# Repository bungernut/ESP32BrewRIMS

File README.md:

# ESP32BrewREMS

# Documentation
I dont know why, but it's been a real pain to find documentation for the ESP32 device. I'm using a HiLetgo ESP32 OLED WiFi Kit V3. This is apparently really a product by Heltec: https://heltec.org/project/wifi-kit32-v3/

USB-Serial Driver: https://www.silabs.com/developer-tools/usb-to-uart-bridge-vcp-drivers

This library seems to be really important https://github.com/HelTecAutomation/Heltec_ESP32

None of their links work, so I'm going to try to scrape together what I can find:  
## Specifications
* Master Chip  ESP32-S3FN8(Xtensa®32-bit lx7 dual core processor)  
* USB to Serial Chip  CP2102  
* WiFi  802.11 b/g/n, up to 150Mbps  
* Bluetooth LE  Bluetooth 5, Bluetooth mesh  
* Hardware Resource  7*ADC1+2*ADC2; 7*Touch; 3*UART; 2*I2C; 2*SPI, etc.  
* Memory  384KB ROM;  512KB SRAM;  16KB RTC SRAM;  8MB SiP Flash  
* 2*1.25 lithium battery interface;  2*18*2.54 Header Pin  
* Battery  3.7V lithium battery power supply and charging  

### Encoder Input
I should have looked at the spec sheet. I think the circuit is close w/ the input pullup:
https://www.digikey.com/en/products/detail/bourns-inc/PEC11H-4220F-S0024/12349532

ledc is a little weird but we're trying to use if for power control (https://docs.espressif.com/projects/arduino-esp32/en/latest/api/ledc.html).
The range of settings is limited between freq and resolution.
Run this script to get the output https://github.com/espressif/arduino-esp32/blob/master/libraries/ESP32/examples/AnalogOut/ledcFrequency/ledcFrequency.ino
```
Bit resolution | Min Frequency [Hz] | Max Frequency [Hz]
             1 |              19532 |           20039138
             2 |               9766 |           10019569
             3 |               4883 |            5009784
             4 |               2442 |            2504892
             5 |               1221 |            1252446
             6 |                611 |             626223
             7 |                306 |             313111
             8 |                153 |             156555
             9 |                 77 |              78277
            10 |                 39 |              39138
            11 |                 20 |              19569
            12 |                 10 |               9784
            13 |                  5 |               4892
            14 |                  3 |               2446
```

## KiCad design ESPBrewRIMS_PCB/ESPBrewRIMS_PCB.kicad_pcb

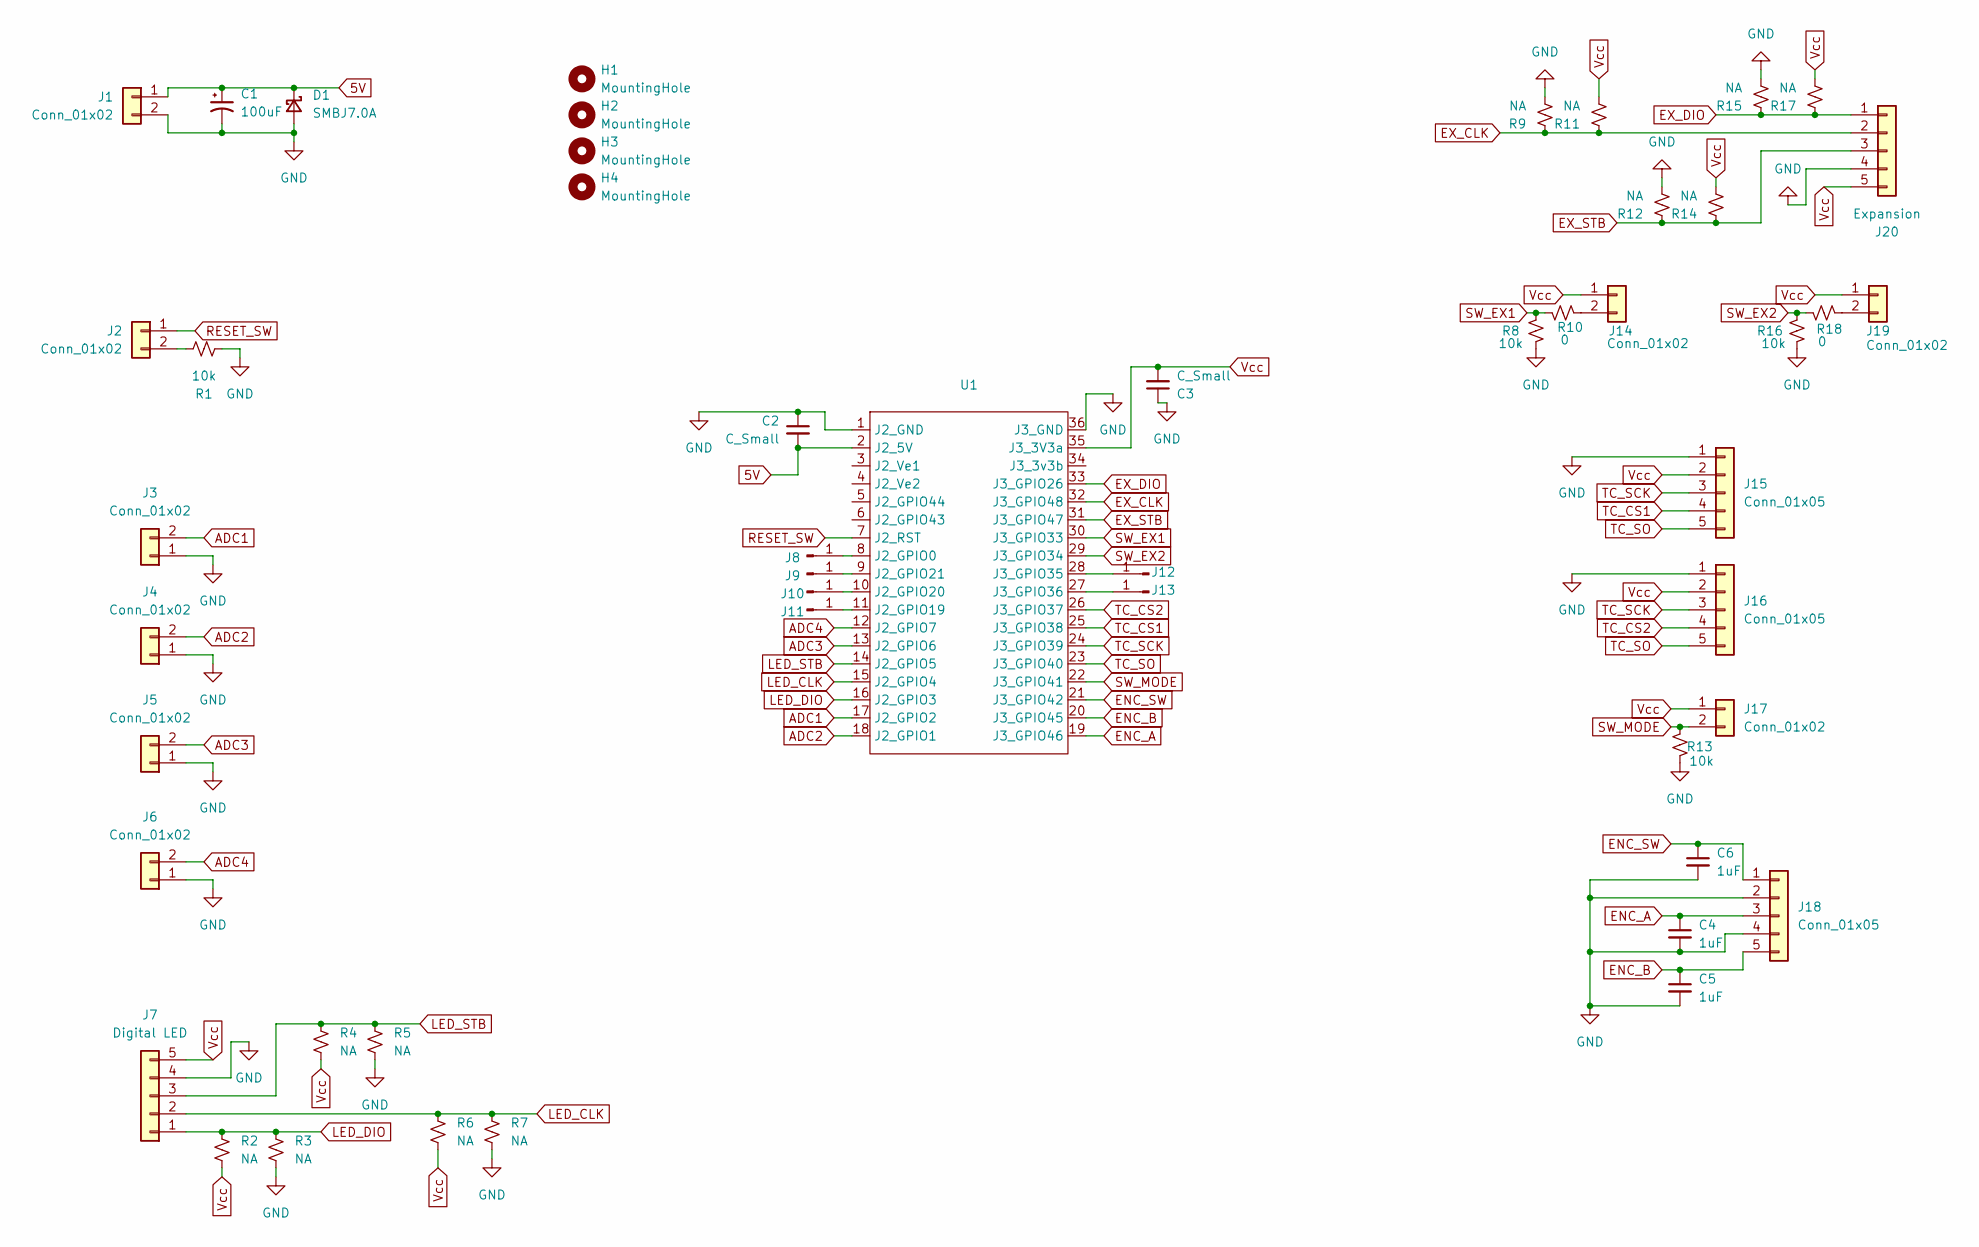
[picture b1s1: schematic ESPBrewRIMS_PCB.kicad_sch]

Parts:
C1: 100uF; CP_Radial_D8.0mm_P3.50mm
C2, C3: C_Small; C_0805_2012Metric_Pad1.18x1.45mm_HandSolder
C4, C5, C6: 1uF; C_0805_2012Metric_Pad1.18x1.45mm_HandSolder
D1: SMBJ7.0A; D_SMA-SMB_Universal_Handsoldering
H1, H2, H3, H4: MountingHole; MountingHole_3mm
J1, J2, J3, J4, J5, J6, J14, J17, J19: Conn_01x02; Molex_SL_171971-0002_1x02_P2.54mm_Vertical
J7: Digital LED; Molex_SL_171971-0005_1x05_P2.54mm_Vertical
J8, J9, J10, J11, J12, J13: Conn_01x01_Pin; PinSocket_1x01_P2.54mm_Vertical
J15, J16, J18: Conn_01x05; Molex_SL_171971-0005_1x05_P2.54mm_Vertical
J20: Expansion; PinHeader_1x05_P2.54mm_Vertical
R1, R8, R13, R16: 10k; R_0805_2012Metric_Pad1.20x1.40mm_HandSolder
R2, R3, R4, R5, R6, R7, R9, R11, R12, R14, R15, R17: NA; R_0805_2012Metric_Pad1.20x1.40mm_HandSolder
R10, R18: 0; R_0805_2012Metric_Pad1.20x1.40mm_HandSolder
U1: DIP-36_907_ELL

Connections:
5V: C1.1, C2.2, D1.1 (K), J1.1, U1.2 (J2_5V)
ADC1: J3.2, U1.17 (J2_GPIO2)
ADC2: J4.2, U1.18 (J2_GPIO1)
ADC3: J5.2, U1.13 (J2_GPIO6)
ADC4: J6.2, U1.12 (J2_GPIO7)
ENC_A: C4.1, J18.3, U1.19 (J3_GPIO46)
ENC_B: C5.1, J18.5, U1.20 (J3_GPIO45)
ENC_SW: C6.1, J18.1, U1.21 (J3_GPIO42)
EX_CLK: J20.2, R9.1, R11.1, U1.32 (J3_GPIO48)
EX_DIO: J20.1, R15.1, R17.1, U1.33 (J3_GPIO26)
EX_STB: J20.3, R12.1, R14.1, U1.31 (J3_GPIO47)
GND: C1.2, C2.1, C3.1, C4.2, C5.2, C6.2, D1.2 (A), J1.2, J3.1, J4.1, J5.1, J6.1, J7.4, J15.1, J16.1, J18.2, J18.4, J20.4, R1.2, R3.2, R5.2, R7.2, R8.2, R9.2, R12.2, R13.2, R15.2, R16.2, U1.1 (J2_GND), U1.36 (J3_GND)
LED_CLK: J7.2, R6.1, R7.1, U1.15 (J2_GPIO4)
LED_DIO: J7.1, R2.1, R3.1, U1.16 (J2_GPIO3)
LED_STB: J7.3, R4.1, R5.1, U1.14 (J2_GPIO5)
unnamed: J2.2, R1.1
unnamed: J8.1, U1.8 (J2_GPIO0)
unnamed: J9.1, U1.9 (J2_GPIO21)
unnamed: J10.1, U1.10 (J2_GPIO20)
unnamed: J11.1, U1.11 (J2_GPIO19)
unnamed: J12.1, U1.28 (J3_GPIO35)
unnamed: J13.1, U1.27 (J3_GPIO36)
unnamed: J14.2, R10.2
unnamed: J19.2, R18.2
RESET_SW: J2.1, U1.7 (J2_RST)
SW_EX1: R8.1, R10.1, U1.30 (J3_GPIO33)
SW_EX2: R16.1, R18.1, U1.29 (J3_GPIO34)
SW_MODE: J17.2, R13.1, U1.22 (J3_GPIO41)
TC_CS1: J15.4, U1.25 (J3_GPIO38)
TC_CS2: J16.4, U1.26 (J3_GPIO37)
TC_SCK: J15.3, J16.3, U1.24 (J3_GPIO39)
TC_SO: J15.5, J16.5, U1.23 (J3_GPIO40)
Vcc: C3.2, J7.5, J14.1, J15.2, J16.2, J17.1, J19.1, J20.5, R2.2, R4.2, R6.2, R11.2, R14.2, R17.2, U1.35 (J3_3V3a)

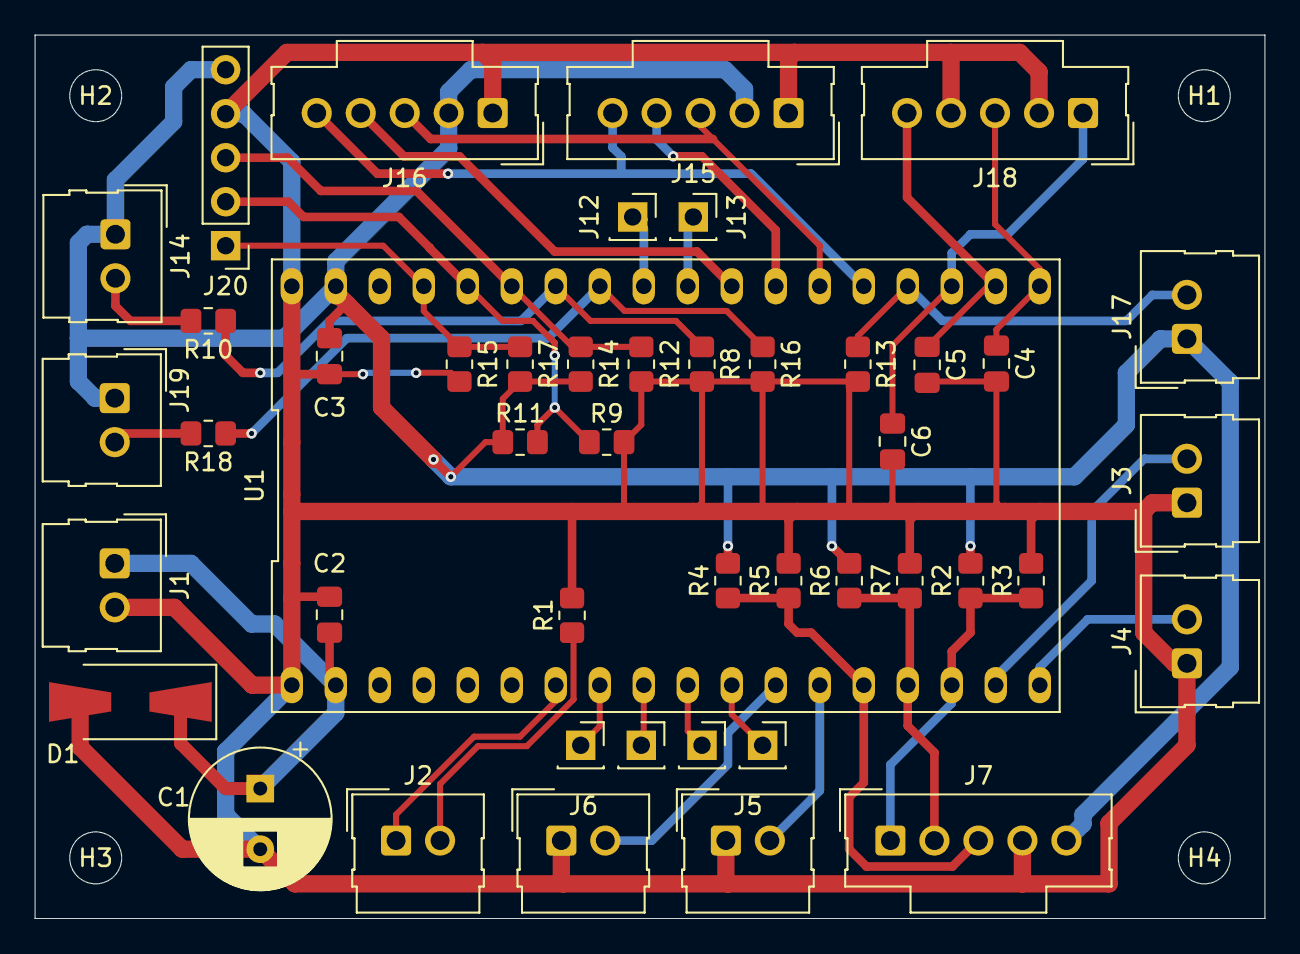
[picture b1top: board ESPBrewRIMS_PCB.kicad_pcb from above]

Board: 2 copper layers, 71.0 x 51.0 mm, 50 parts (0 on the bottom side), 33 nets.

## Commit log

2025-02-27 initial
2025-02-28 getting display working and thinking about logic
2025-03-01 A UI working now w/ encoder and enable switch
2025-03-03 Got TC and DigitalLEDs working
2025-03-04 second TC working now
2025-03-04 ignore kicad backups
2025-03-04 add kicad files wip
2025-03-04 Partially assigned footprints
2025-03-05 Sent version to JLCPCB for print
2025-03-05 updated encoder cap values
2025-03-07 added PID to control LED
2025-03-17 removed encoder, struggling w/ LEDs
2025-03-17 added AC sch
2025-03-20 thinking about MQTT control instead
2025-03-31 code worked for first brew
2025-08-26 adding code for WEB based control
2025-08-29 working WEB interface now
2025-09-03 brewed with this version, removed useless sensor
